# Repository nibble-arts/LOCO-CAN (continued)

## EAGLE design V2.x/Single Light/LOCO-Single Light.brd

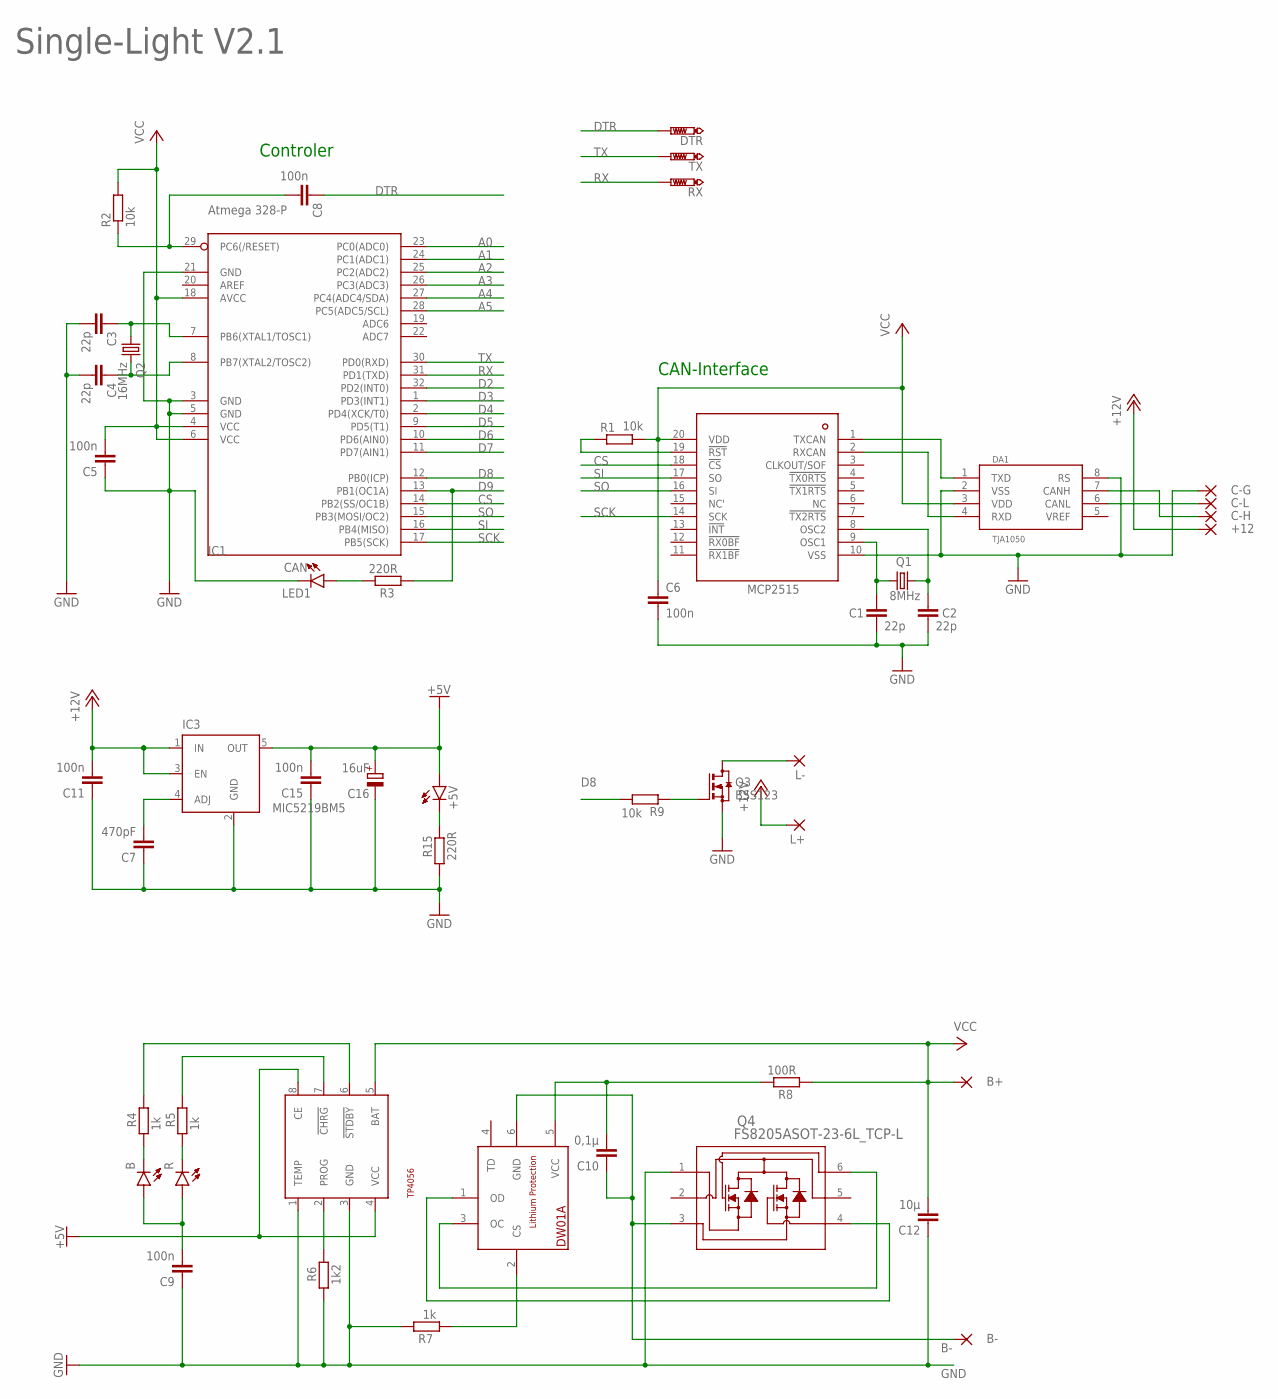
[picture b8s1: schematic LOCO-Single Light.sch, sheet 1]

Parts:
+5V: LEDCHIP-LED0603; CHIP-LED0603
+12: 1,6/0,8
B: LEDCHIP-LED0603; CHIP-LED0603
B+: 1,6/0,8
B-: 1,6/0,8
C1, C2, C3, C4: 22p; C0402K
C5, C6, C8, C9, C11, C15: 100n; C0402K
C7: 470pF; C0402K
C10: 0,1µ; C0402K
C12: 10µ; C0402K
C16: 16uF; A/3216-18W
C-G: 1,6/0,8
C-H: 1,6/0,8
C-L: 1,6/0,8
CAN: LED1; LEDC1608X39N_B
DA1: TJA1050; SO08
DTR: PTR1B1,27; B1,27
IC1: Atmega 328-P; TQFP32-08
IC2: MCP2515; TSSOP20
IC3: MIC5219BM5; SOT23-5
IC4: TP4056; SOT23-8
IC5: DW01A; SOT23-6
L+: 1,6/0,8
L-: 1,6/0,8
Q1: 8MHz; 5.0X3.2_2
Q2: 16MHz; 5.0X3.2_2
Q3: BSS123; SOT23
Q4: FS8205ASOT-23-6L_TCP-L; SOT-23-6L_TCP-L
R: LEDCHIP-LED0603; CHIP-LED0603
R1, R2, R9: 10k; R0402
R3, R15: 220R; R0402
R4, R5, R7: 1k; R0402
R6: 1k2; R0402
R8: 100R; R0402
RX: PTR1B1,27; B1,27
TX: PTR1B1,27; B1,27

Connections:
+5V: +5V.A, C15.2, C16.+, IC3.5 (OUT), IC4.4 (VCC), IC4.8 (CE)
+12V: +12.1, C11.2, IC3.1 (IN), IC3.3 (EN), L+.1
A0: IC1.23 (PC0(ADC0))
A1: IC1.24 (PC1(ADC1))
A2: IC1.25 (PC2(ADC2))
A3: IC1.26 (PC3(ADC3))
A4: IC1.27 (PC4(ADC4/SDA))
A5: IC1.28 (PC5(ADC5/SCL))
B-: B-.1, C10.1, IC5.6 (GND), Q4.3
CAN-H: C-H.1, DA1.7 (CANH)
CAN-L: C-L.1, DA1.6 (CANL)
CAN-OCC1: C1.1, IC2.9 (OSC1), Q1.1
CAN-OCC2: C2.1, IC2.8 (OSC2), Q1.2
CS: IC1.14 (PB2(SS/OC1B)), IC2.18 (!CS)
D2: IC1.32 (PD2(INT0))
D3: IC1.1 (PD3(INT1))
D4: IC1.2 (PD4(XCK/T0))
D5: IC1.9 (PD5(T1))
D6: IC1.10 (PD6(AIN0))
D7: IC1.11 (PD7(AIN1))
D8: IC1.12 (PB0(ICP)), R9.2
D9: IC1.13 (PB1(OC1A)), R3.1
DTR: C8.1, DTR.TP
GND: C1.2, C2.2, C3.2, C4.2, C5.1, C6.2, C7.1, C9.1, C11.1, C12.1, C15.1, C16.-, C-G.1, CAN.1 (C), DA1.2 (VSS), DA1.8 (RS), IC1.3 (GND), IC1.5 (GND), IC1.21 (GND), IC2.10 (VSS), IC3.2 (GND), IC4.1 (TEMP), IC4.3 (GND), Q3.2 (S), Q4.1, R6.1, R7.2, R15.1
LIGHT: L-.1, Q3.3 (D)
unnamed: C7.2, IC3.4 (ADJ)
unnamed: Q3.1 (G), R9.1
unnamed: CAN.2 (A), R3.2
unnamed: B.C, R4.1
unnamed: R.C, R5.1
unnamed: IC2.19 (!RST), R1.1
unnamed: IC4.6 (!STDBY), R4.2
unnamed: IC4.7 (!CHRG), R5.2
unnamed: IC4.2 (PROG), R6.2
unnamed: C3.1, IC1.7 (PB6(XTAL1/TOSC1)), Q2.1
unnamed: C4.1, IC1.8 (PB7(XTAL2/TOSC2)), Q2.2
unnamed: +5V.C, R15.2
unnamed: B.A, C9.2, R.A
unnamed: IC5.3 (OC), Q4.6
unnamed: C8.2, IC1.29 (PC6(/RESET)), R2.1
unnamed: IC5.1 (OD), Q4.4
unnamed: C10.2, IC5.5 (VCC), R8.2
unnamed: IC5.2 (CS), R7.1
RX: IC1.31 (PD1(TXD)), RX.TP
RXCAN: DA1.4 (RXD), IC2.2 (RXCAN)
SCK: IC1.17 (PB5(SCK)), IC2.14 (SCK)
SI: IC1.16 (PB4(MISO)), IC2.17 (SO)
SO: IC1.15 (PB3(MOSI/OC2)), IC2.16 (SI)
TX: IC1.30 (PD0(RXD)), TX.TP
TXCAN: DA1.1 (TXD), IC2.1 (TXCAN)
VCC: B+.1, C5.2, C6.1, C12.2, DA1.3 (VDD), IC1.4 (VCC), IC1.6 (VCC), IC1.18 (AVCC), IC2.20 (VDD), IC4.5 (BAT), R1.2, R2.2, R8.1

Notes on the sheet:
CAN-Interface
Controler
Single-Light V2.1

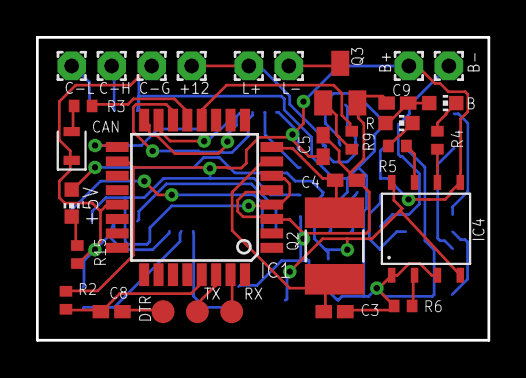
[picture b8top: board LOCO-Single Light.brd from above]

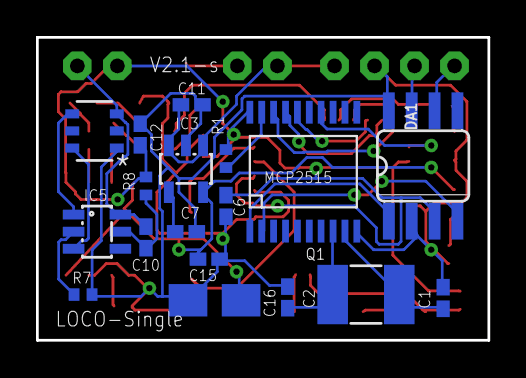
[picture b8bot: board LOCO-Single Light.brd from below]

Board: 2 copper layers, 25.1 x 16.8 mm, 49 parts (18 on the bottom side), 39 nets.

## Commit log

2023-02-03 initial
2023-02-03 Update of program cable and tripple LED
2023-02-15 Bugfix in motor driver schematics and board
